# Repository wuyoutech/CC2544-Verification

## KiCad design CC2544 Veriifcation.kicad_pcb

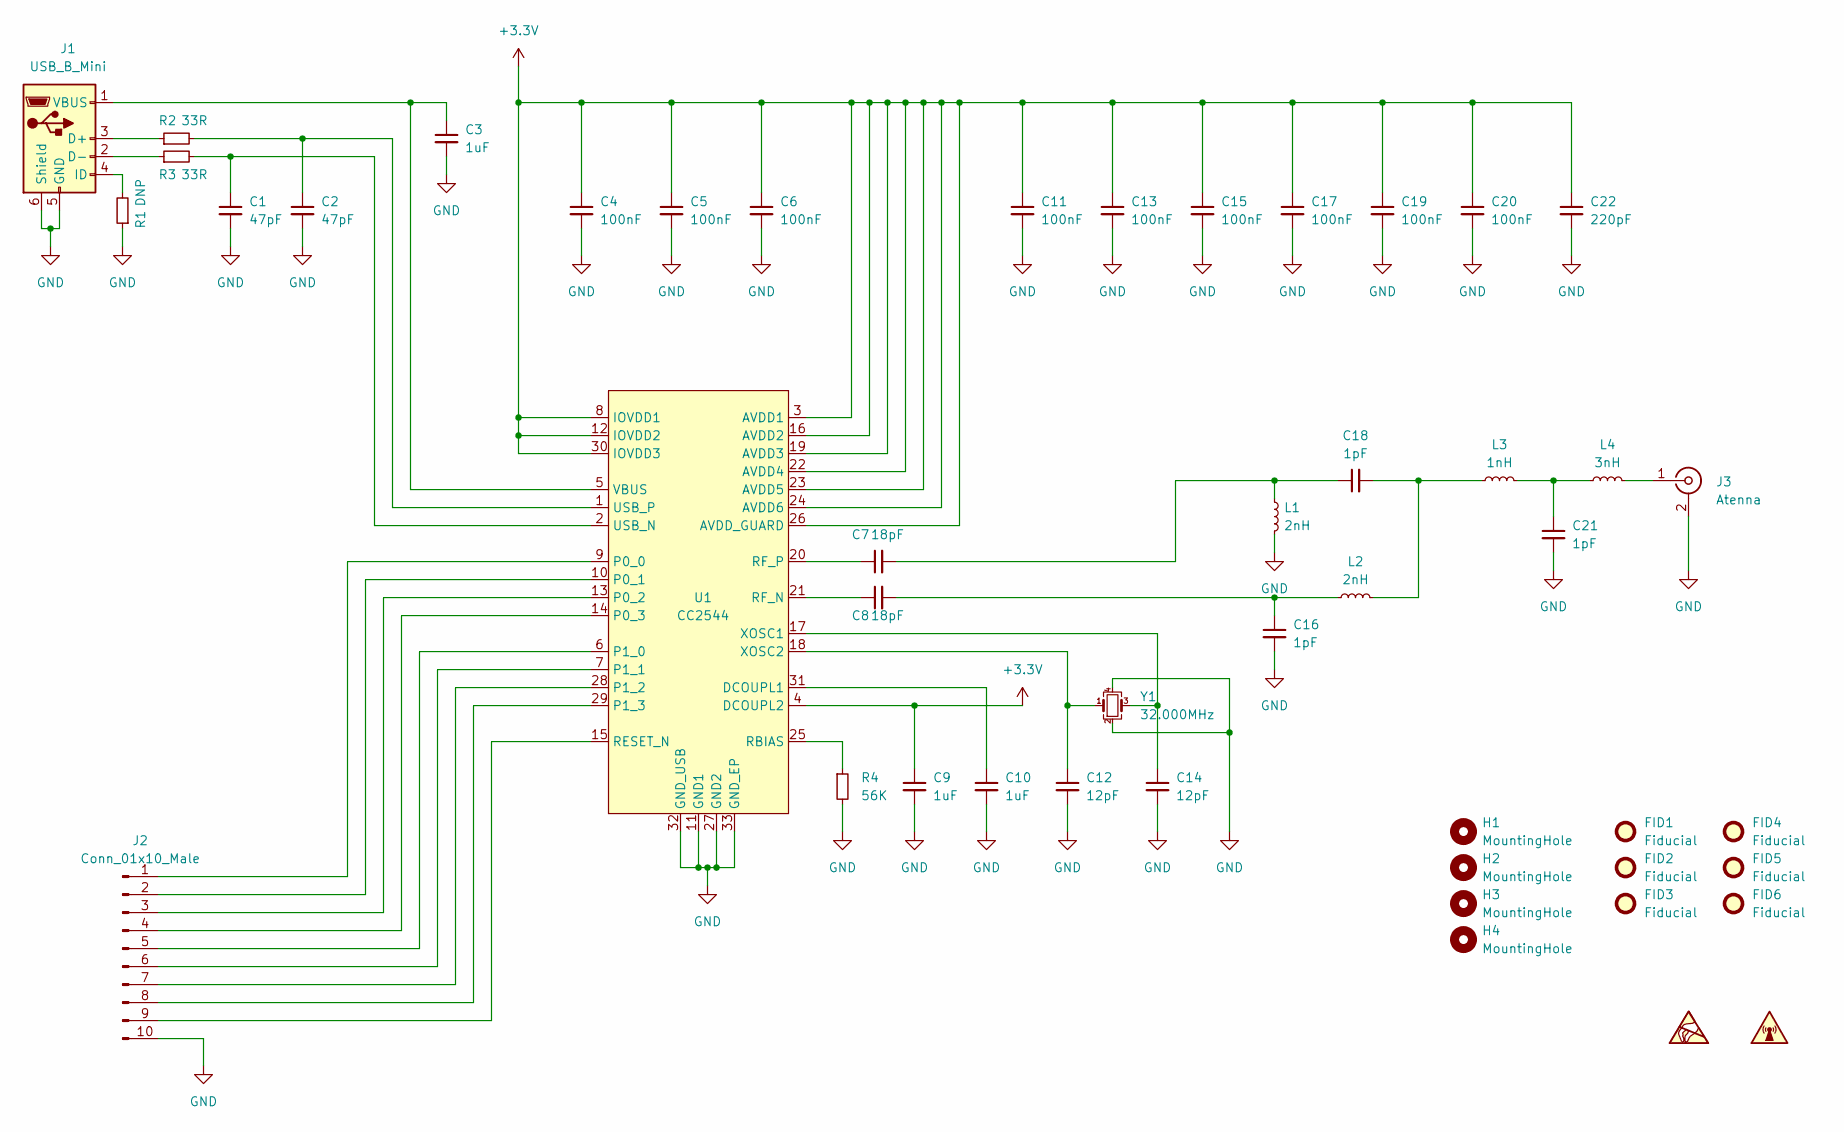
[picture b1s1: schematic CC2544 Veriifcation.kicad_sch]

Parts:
C1, C2: 47pF; C_0402_1005Metric
C3, C9, C10: 1uF; C_0402_1005Metric
C4, C5, C6, C11, C13, C15, C17, C19, C20: 100nF; C_0402_1005Metric
C7, C8: 18pF; C_0402_1005Metric
C12, C14: 12pF; C_0402_1005Metric
C16, C18, C21: 1pF; C_0402_1005Metric
C22: 220pF; C_0402_1005Metric
FID1, FID2, FID3, FID4, FID5, FID6: Fiducial; Fiducial_0.5mm_Mask1.5mm
H1, H2, H3, H4: MountingHole; MountingHole_2.7mm_M2.5_DIN965
J1: USB_B_Mini; USB_Micro-B_Molex-105017-0001
J2: Conn_01x10_Male; PinHeader_1x10_P2.54mm_Vertical
J3: Atenna; SMA_Amphenol_132134-11_Vertical
L1, L2: 2nH; L_0402_1005Metric
L3: 1nH; L_0402_1005Metric
L4: 3nH; L_0402_1005Metric
R1: DNP; R_0402_1005Metric
R2, R3: 33R; R_0402_1005Metric
R4: 56K; R_0402_1005Metric
U1: CC2544; QFN-32-1EP_5x5mm_P0.5mm_EP3.45x3.45mm
Y1: 32.000MHz; Crystal_SMD_1612-4Pin_1.6x1.2mm

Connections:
+3V3: C4.1, C5.1, C6.1, C9.1, C11.1, C13.1, C15.1, C17.1, C19.1, C20.1, C22.1, U1.3 (AVDD1), U1.4 (DCOUPL2), U1.8 (IOVDD1), U1.12 (IOVDD2), U1.16 (AVDD2), U1.19 (AVDD3), U1.22 (AVDD4), U1.23 (AVDD5), U1.24 (AVDD6), U1.26 (AVDD_GUARD), U1.30 (IOVDD3)
GND: C1.2, C2.2, C3.2, C4.2, C5.2, C6.2, C9.2, C10.2, C11.2, C12.2, C13.2, C14.2, C15.2, C16.2, C17.2, C19.2, C20.2, C21.2, C22.2, J1.5 (GND), J1.6 (Shield), J2.10, J3.2 (Ext), L1.2, R1.1, R4.2, U1.11 (GND1), U1.27 (GND2), U1.32 (GND_USB), U1.33 (GND_EP), Y1.2, Y1.4
unnamed: C1.1, R3.2, U1.2 (USB_N)
unnamed: C2.1, R2.2, U1.1 (USB_P)
unnamed: C3.1, J1.1 (VBUS), U1.5 (VBUS)
unnamed: C7.1, U1.20 (RF_P)
unnamed: C8.1, U1.21 (RF_N)
unnamed: C10.1, U1.31 (DCOUPL1)
unnamed: C12.1, U1.18 (XOSC2), Y1.1
unnamed: C14.1, U1.17 (XOSC1), Y1.3
unnamed: C8.2, C16.1, L2.1
unnamed: C7.2, C18.1, L1.1
unnamed: C18.2, L2.2, L3.1
unnamed: C21.1, L3.2, L4.1
unnamed: J1.2 (D-), R3.1
unnamed: J1.3 (D+), R2.1
unnamed: J1.4 (ID), R1.2
unnamed: J2.1, U1.9 (P0_0)
unnamed: J2.2, U1.10 (P0_1)
unnamed: J2.3, U1.13 (P0_2)
unnamed: J2.4, U1.14 (P0_3)
unnamed: J2.5, U1.6 (P1_0)
unnamed: J2.6, U1.7 (P1_1)
unnamed: J2.7, U1.28 (P1_2)
unnamed: J2.8, U1.29 (P1_3)
unnamed: J2.9, U1.15 (RESET_N)
unnamed: J3.1 (In), L4.2
unnamed: R4.1, U1.25 (RBIAS)

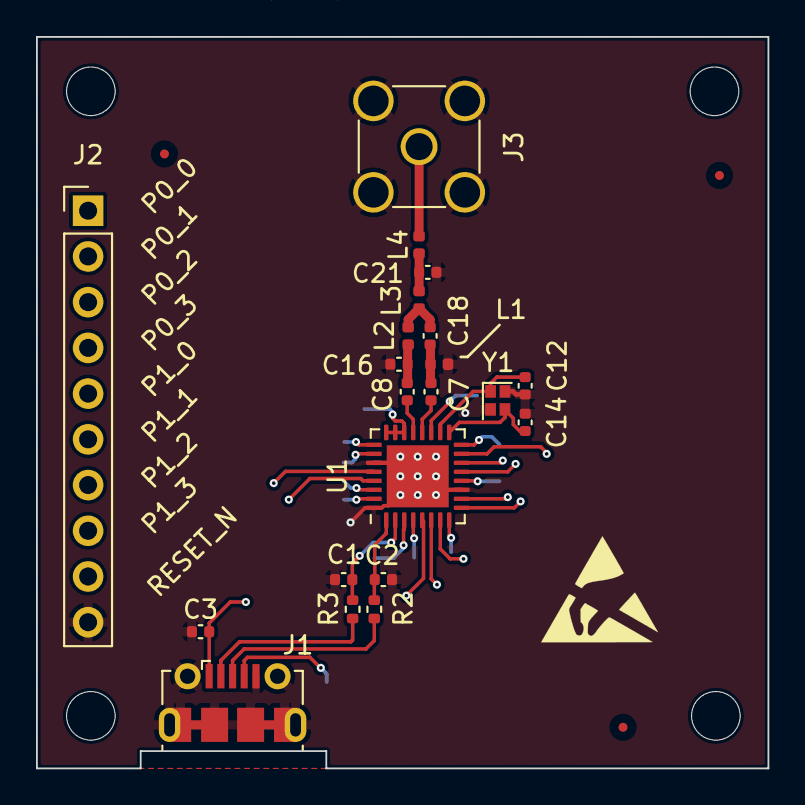
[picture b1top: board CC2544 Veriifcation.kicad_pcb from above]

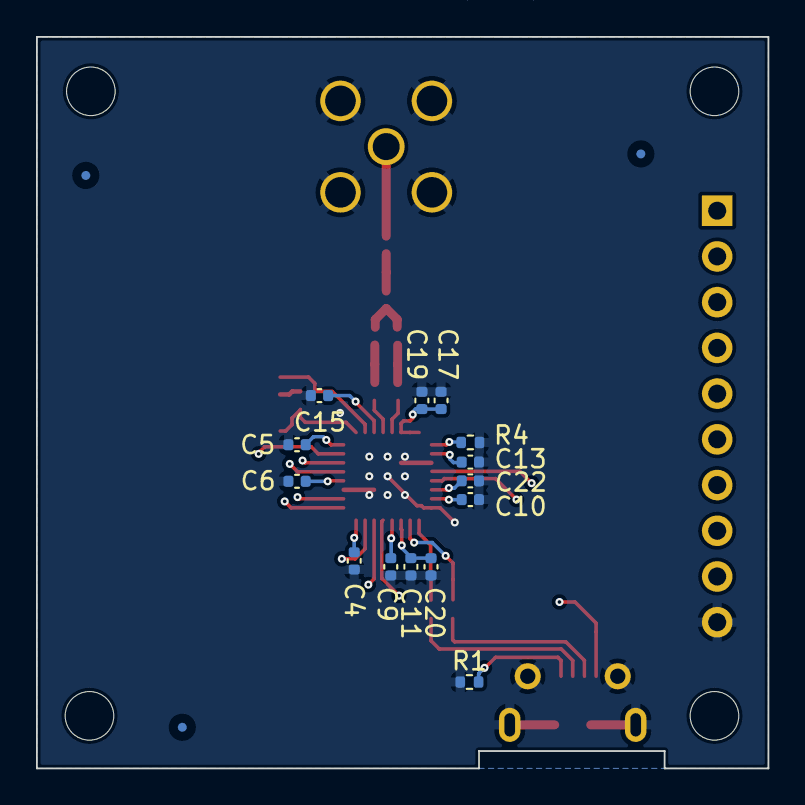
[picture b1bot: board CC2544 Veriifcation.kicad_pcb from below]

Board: 4 copper layers, 40.6 x 40.6 mm, 45 parts (17 on the bottom side), 28 nets.

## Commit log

2021-10-24 Init Commit
2021-10-26 release_v1.0
2021-11-22 add GPIO silkscreen
